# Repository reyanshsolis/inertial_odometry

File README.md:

# AGV_Encoders_IMU

# Project Goal

To develope accurate and precise encoders using two Innertial Mesurement Units

# Components Used

1. IMU
2. Communication Modules(XBEE or NRF)
3. Arduino Nano
4. Arduino Mega
5. 9V Battery

# Description

This paper describes the design and development of a non-intrusive inertial sensor used for determining the odometry of a ground vehicle. The sensors are meant to be placed on the rim of the wheels of a ground vehicle and determine the angular velocity of wheels and the angular velocity of the vehicle about its center axis perpendicular to the ground plane. The mathematical model incorporates the electronic gyroscope data of left and right wheel sensor and the relationship between the angular velocity about the central axis of wheels on either side while turning, to calculate the turning angular velocity of car and angular velocities of wheels which in turn determines the linear velocity of the car. These sensors can be used to replace the conventional optical or hall-effect based speed sensors which are difficult to be used with existing models of the ground vehicle as they require specific placement and specially designed mounts. 
The primary advantage of this sensor is that it can be placed at any position on the wheel, at any angle with respect to the wheel plane. The determined parameters do not depend on the placement of the sensor on the wheel in any way, as it only requires the resultant of angular velocities on each tire. Multiple noises and bias filters such as Kalman Filter for bias reduction and Extended Kalman Filter and Madgwick Filter among others for noise reduction have been tested on this model and the obtained results have been compared and analyzed in this paper with respect to the quality of the output, computation time and resultant lag.
Different modules for wireless communication (nrf24l01+, Zigbee Xbee S2C) were also used for obtaining the best performance for this specific purpose and the results have been analyzed in terms of data rate, range and security, and reliability among others. This sensor has been tested on different types of vehicles such as cars, rickshaws and mobile robots such as Husky and Jackal under varying road conditions and the performance was compared with optical encoders that are currently being used for odometry estimation.

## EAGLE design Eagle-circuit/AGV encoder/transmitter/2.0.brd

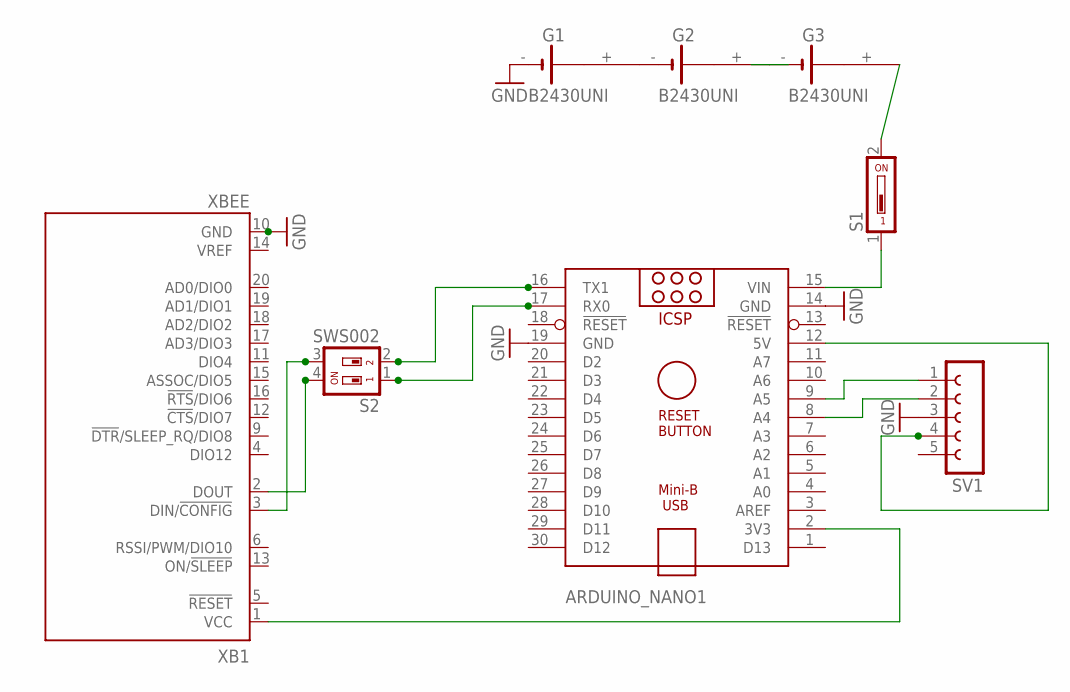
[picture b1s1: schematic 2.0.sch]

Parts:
ARDUINO_NANO1: ARDUINO_NANO
G1, G2, G3: B2430UNI
S1: DS01; DS-01
S2: SWS002; SMS-002
SV1: FE05-1
XB1: XBEE

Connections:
GND: ARDUINO_NANO1.14 (GND), ARDUINO_NANO1.19 (GND), G1.-, SV1.3, XB1.10 (GND)
unnamed: G1.+, G2.-
unnamed: G2.+@1 (+), G3.-
unnamed: G2.+, G3.-@1 (-)
unnamed: G3.+, S1.2
unnamed: ARDUINO_NANO1.15 (VIN), S1.1
unnamed: S2.4, XB1.2 (DOUT)
unnamed: ARDUINO_NANO1.17 (RX0), S2.1
unnamed: ARDUINO_NANO1.16 (TX1), S2.2
unnamed: S2.3, XB1.3 (DIN/!CONFIG)
unnamed: ARDUINO_NANO1.2 (3V3), XB1.1 (VCC)
unnamed: ARDUINO_NANO1.9 (A5), SV1.1
unnamed: ARDUINO_NANO1.8 (A4), SV1.2
unnamed: ARDUINO_NANO1.12 (5V), SV1.4

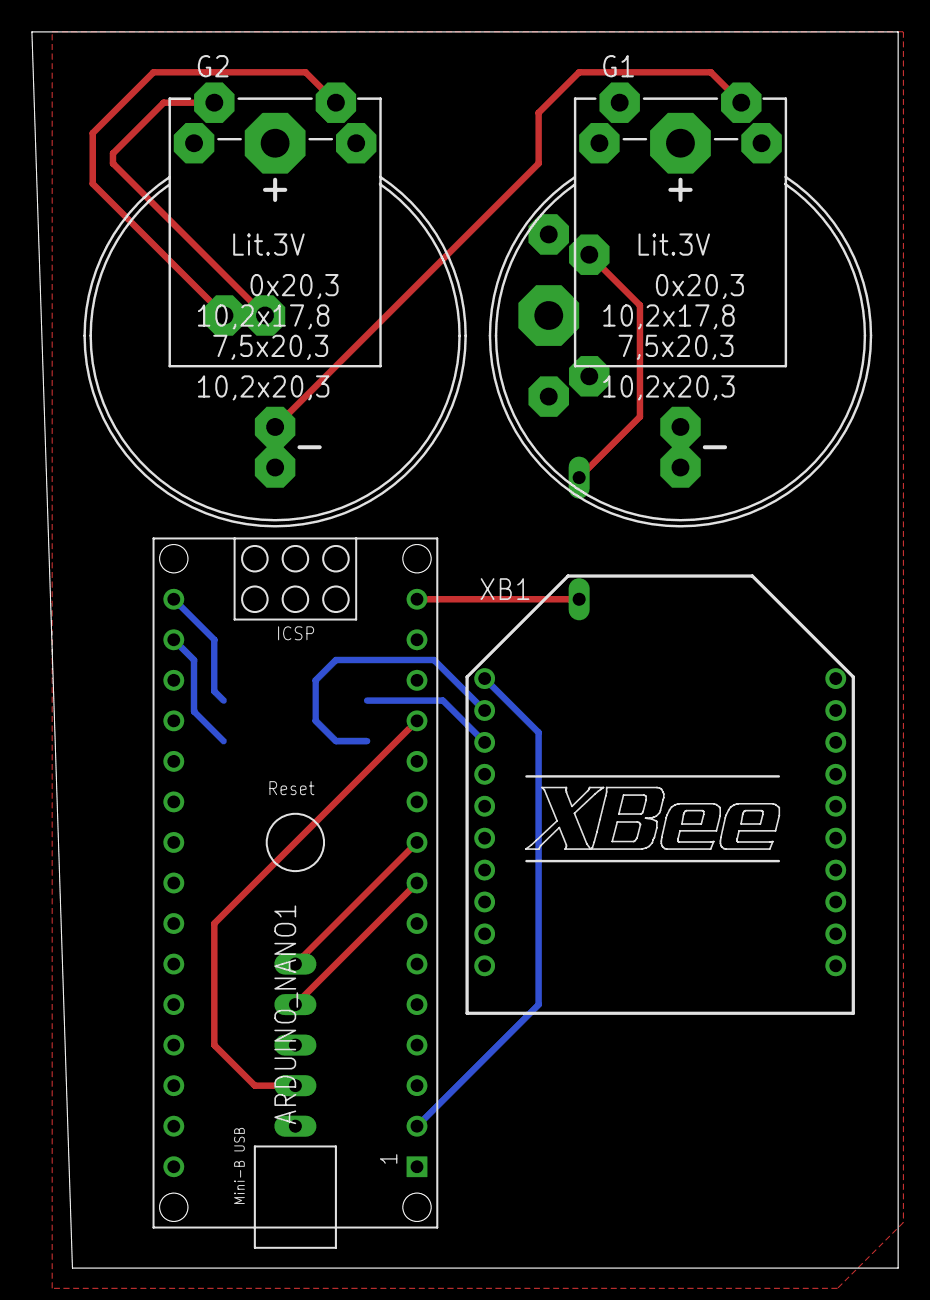
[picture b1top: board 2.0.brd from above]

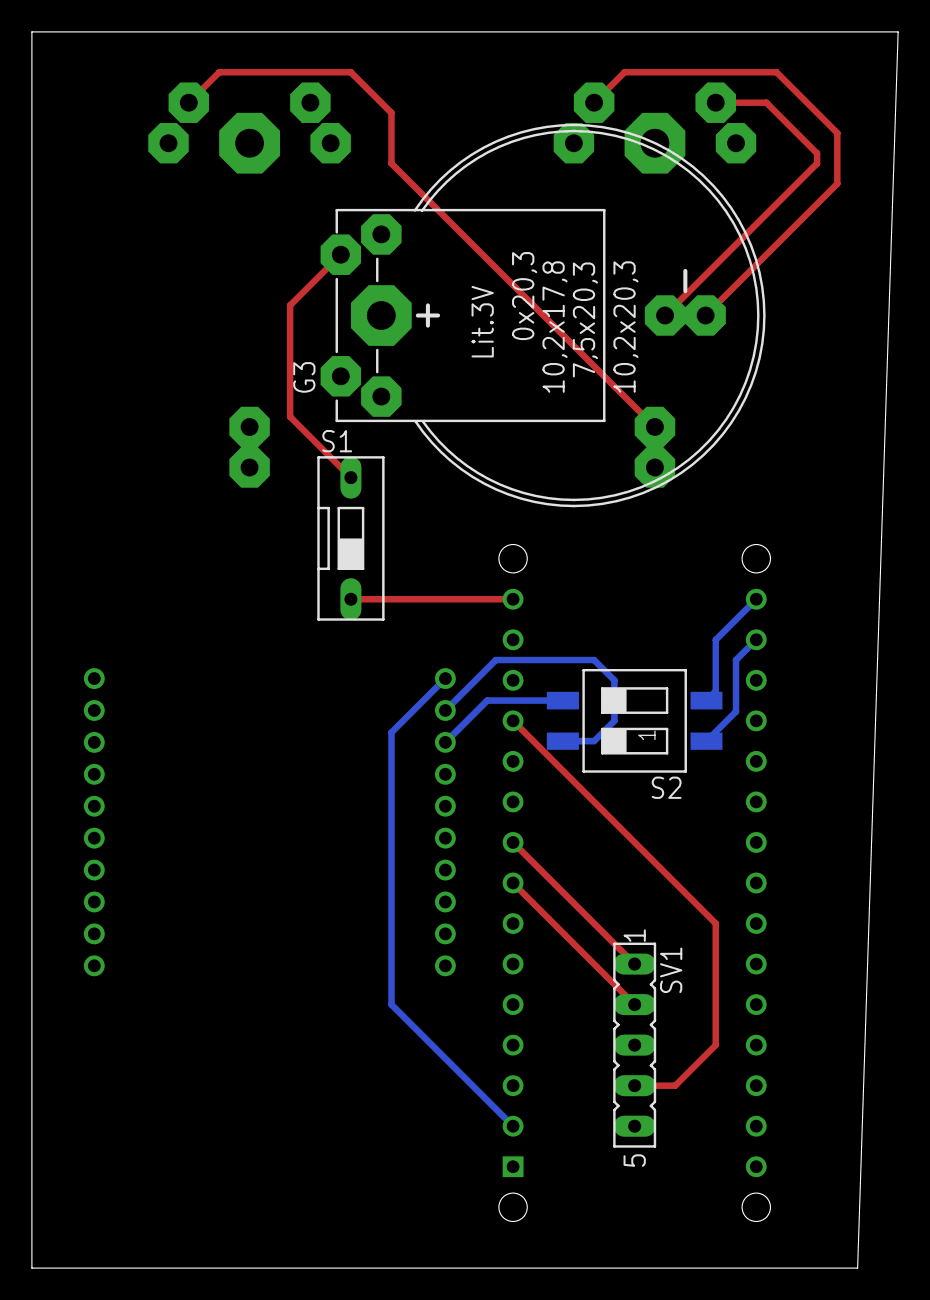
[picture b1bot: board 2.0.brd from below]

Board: 2 copper layers, 54.3 x 77.5 mm, 8 parts (4 on the bottom side), 14 nets.

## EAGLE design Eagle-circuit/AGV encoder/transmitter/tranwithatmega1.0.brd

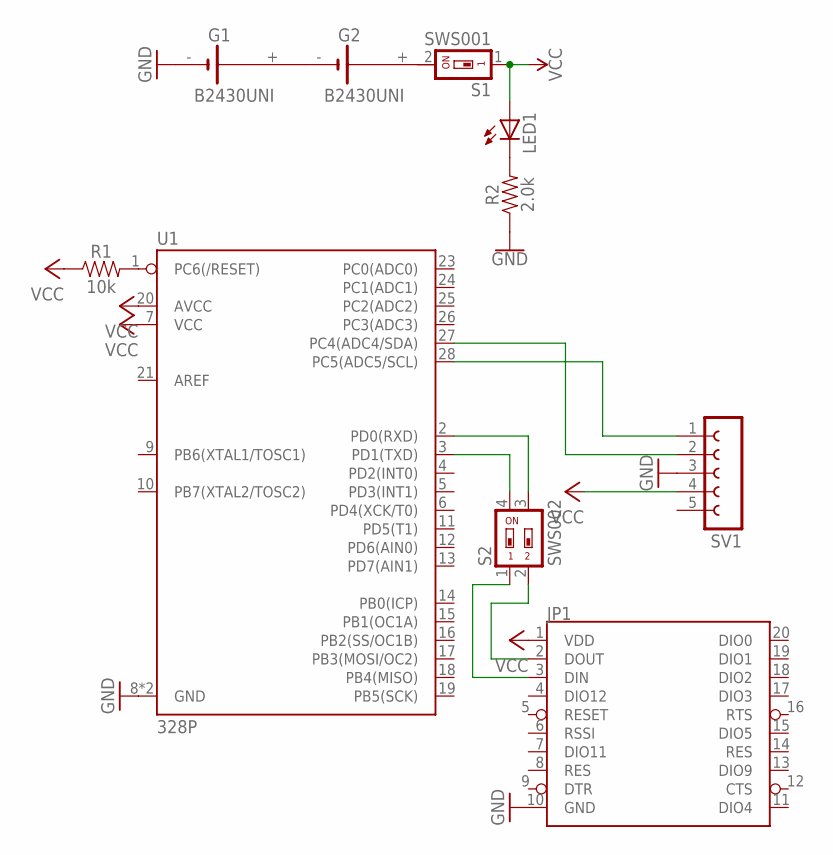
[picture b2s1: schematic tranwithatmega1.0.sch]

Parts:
G1, G2: B2430UNI
JP1: XBEE
LED1: LED_E; LED_1206
R1: 10k; AXIAL-0.3
R2: 2.0k; 0603
S1: SWS001; SMS-001
S2: SWS002; SMS-002
SV1: FE05-1
U1: 328P; DIP28

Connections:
GND: G1.-, JP1.10 (GND), R2.1, SV1.3, U1.8 (GND), U1.22 (GND)
unnamed: R1.P$2 (2), U1.1 (PC6(/RESET))
unnamed: SV1.1, U1.28 (PC5(ADC5/SCL))
unnamed: SV1.2, U1.27 (PC4(ADC4/SDA))
unnamed: S2.3, U1.2 (PD0(RXD))
unnamed: JP1.3 (DIN), S2.1
unnamed: G1.+, G2.-
unnamed: G2.+@1 (+), S1.2
unnamed: S2.4, U1.3 (PD1(TXD))
unnamed: JP1.2 (DOUT), S2.2
unnamed: LED1.C, R2.2
VCC: JP1.1 (VDD), LED1.A, R1.P$1 (1), S1.1, SV1.4, U1.7 (VCC), U1.20 (AVCC)

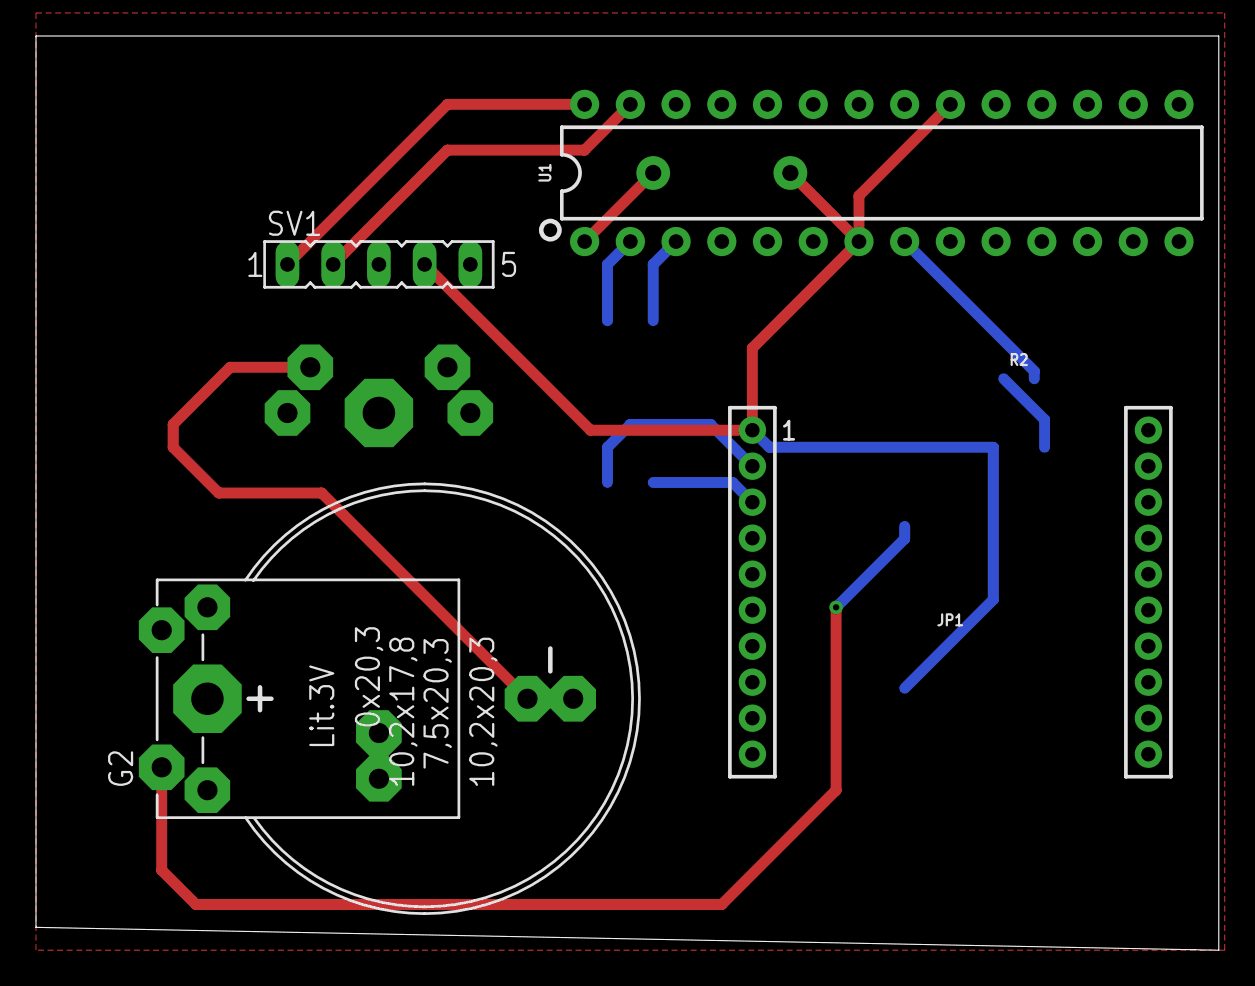
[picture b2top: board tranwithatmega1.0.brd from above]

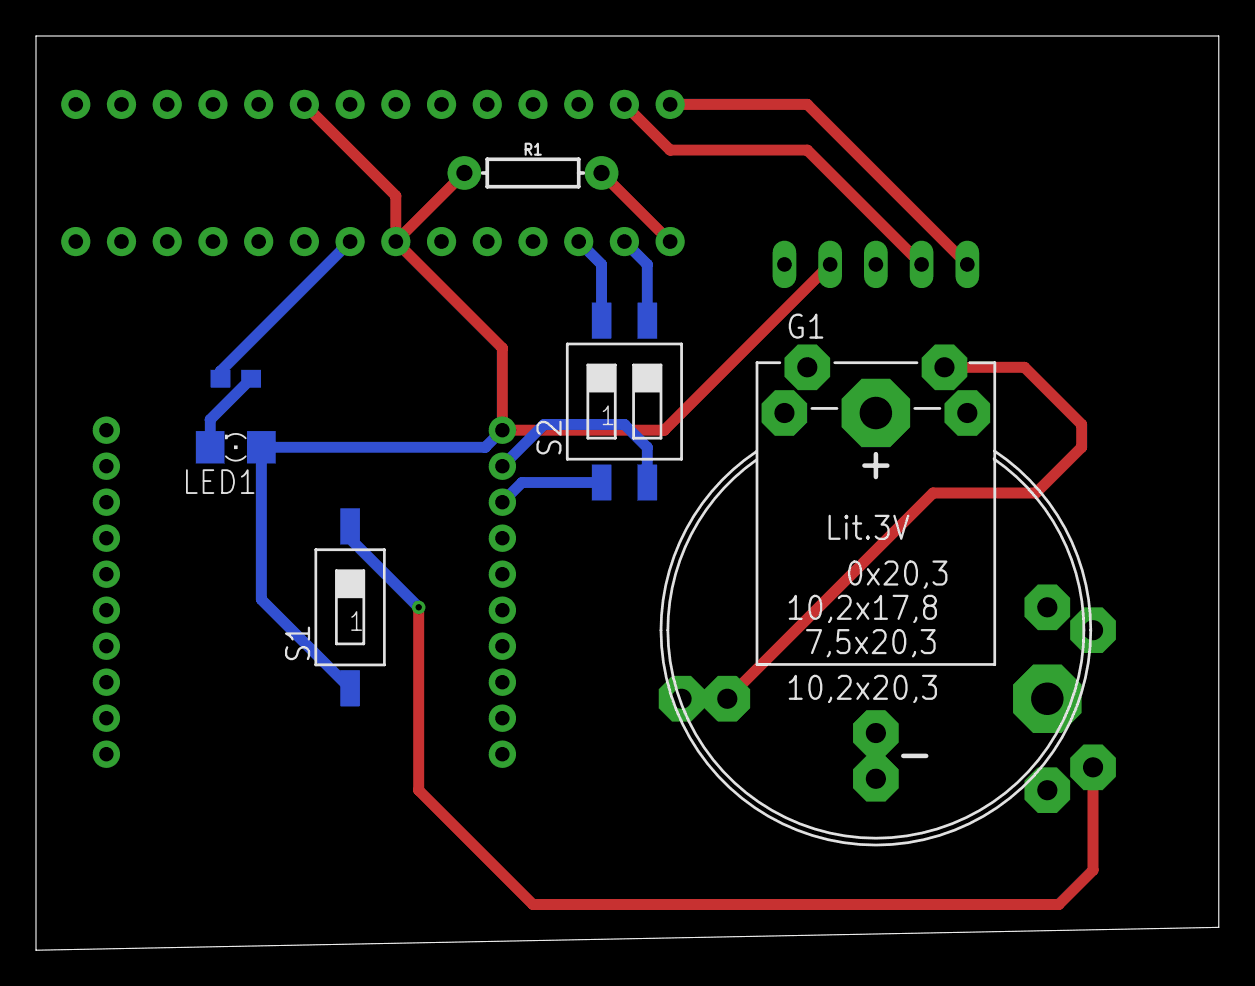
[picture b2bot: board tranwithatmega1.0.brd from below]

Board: 2 copper layers, 65.7 x 50.8 mm, 10 parts (6 on the bottom side), 12 nets.

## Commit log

2019-09-26 Folders Init
2019-09-26 Results Added
2019-10-07 documentation

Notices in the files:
parts and their libraries:
SparkFun-RF: Licensing: Creative Commons ShareAlike 4.0 International - https://creativecommons.org/licenses/by-sa/4.0
